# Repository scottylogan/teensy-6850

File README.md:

# Simple Teensy 3.2 Emulator for Motorola 6850

TBD

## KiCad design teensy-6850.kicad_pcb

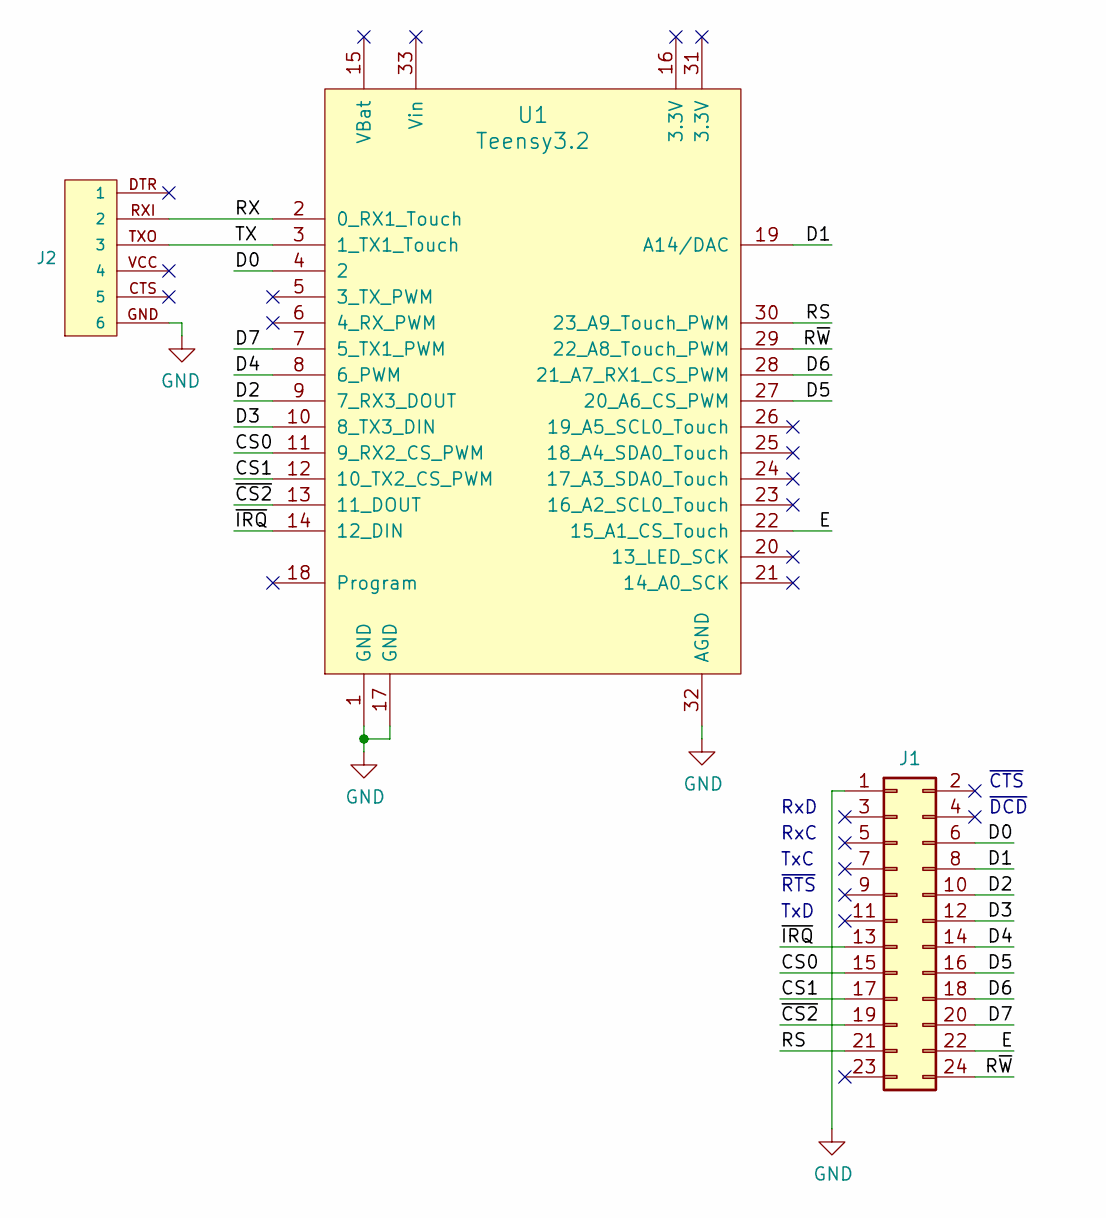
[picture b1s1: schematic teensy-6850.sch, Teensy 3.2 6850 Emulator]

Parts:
J1: Conn_02x12_Odd_Even; IDC-Header_2x12_P2.54mm_Vertical
J2: 6_PIN_SERIAL_CABLEPTH; FTDI_BASIC
U1: Teensy3.2; Teensy32

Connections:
/CS0: J1.15, U1.11 (9_RX2_CS_PWM)
/CS1: J1.17, U1.12 (10_TX2_CS_PWM)
/D0: J1.6, U1.4 (2)
/D1: J1.8, U1.19 (A14/DAC)
/D2: J1.10, U1.9 (7_RX3_DOUT)
/D3: J1.12, U1.10 (8_TX3_DIN)
/D4: J1.14, U1.8 (6_PWM)
/D5: J1.16, U1.27 (20_A6_CS_PWM)
/D6: J1.18, U1.28 (21_A7_RX1_CS_PWM)
/D7: J1.20, U1.7 (5_TX1_PWM)
/E: J1.22, U1.22 (15_A1_CS_Touch)
/RS: J1.21, U1.30 (23_A9_Touch_PWM)
/RX: J2.RXI (2), U1.2 (0_RX1_Touch)
/R~W: J1.24, U1.29 (22_A8_Touch_PWM)
/TX: J2.TXO (3), U1.3 (1_TX1_Touch)
/~CS2: J1.19, U1.13 (11_DOUT)
/~IRQ: J1.13, U1.14 (12_DIN)
GND: J1.1, J2.GND (6), U1.1 (GND), U1.17 (GND), U1.32 (AGND)

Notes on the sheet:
~CTS
~DCD
RxD
RxC
TxD
TxC
~RTS

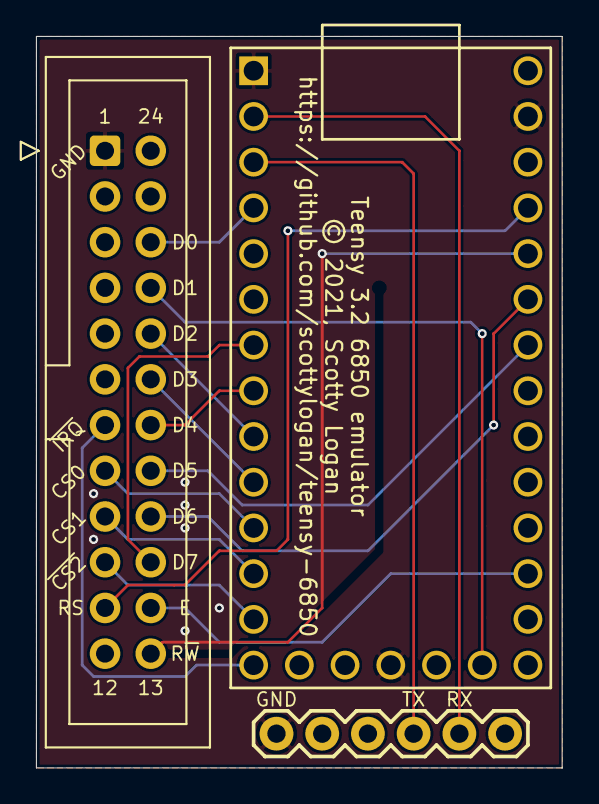
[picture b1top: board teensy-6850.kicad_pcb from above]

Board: 2 copper layers, 29.2 x 40.6 mm, 3 parts (0 on the bottom side), 18 nets.

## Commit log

2021-05-23 moved hardware design into hw subdir

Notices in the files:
teensy-6850.kicad_pcb:
© 2021, Scotty Logan
